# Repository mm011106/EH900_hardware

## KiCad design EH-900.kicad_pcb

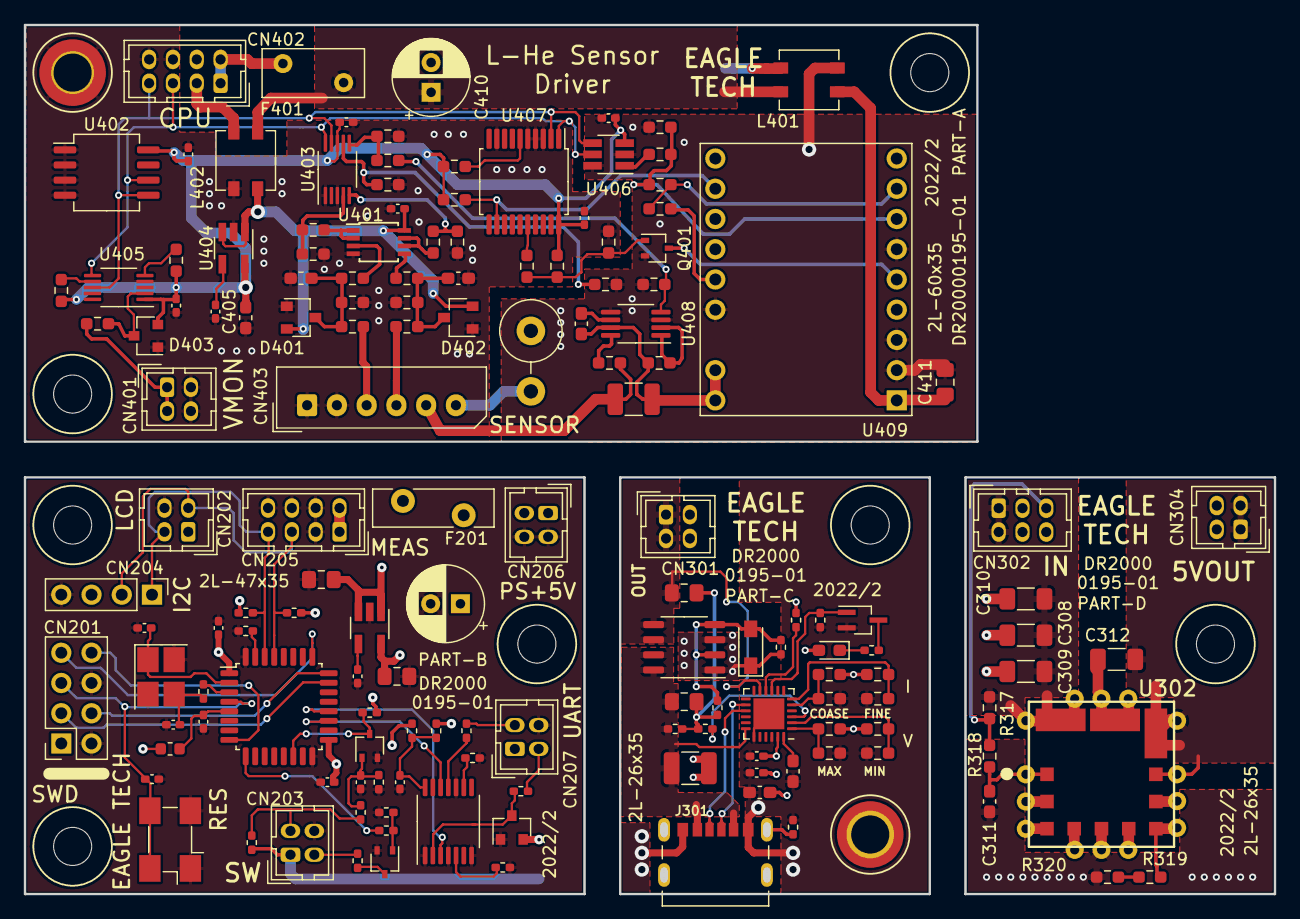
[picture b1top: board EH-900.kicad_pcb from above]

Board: 2 copper layers, 105.0 x 73.0 mm, 151 parts (0 on the bottom side), 101 nets.

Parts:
C201, C202: 6p; C_0402_1005Metric_Pad0.74x0.62mm_HandSolder
C203, C204, C205, C206, C208, C209, C303, C304, C402, C406, C407, C408, C409, C412: 0.1u/16V; C_0402_1005Metric_Pad0.74x0.62mm_HandSolder
C210, C410: 56u/10V/OS; CP_Radial_D6.3mm_P2.50mm
C211, C213: 4.7u/25V; C_0805_2012Metric_Pad1.18x1.45mm_HandSolder
C212, C405: 10n; C_0402_1005Metric_Pad0.74x0.62mm_HandSolder
C301, C306: 1u/50V; C_0603_1608Metric_Pad1.08x0.95mm_HandSolder
C302: 3.3u/50V; C_1210_3225Metric_Pad1.33x2.70mm_HandSolder
C305, C307: 1u/50V; C_0805_2012Metric_Pad1.18x1.45mm_HandSolder
C308, C309, C310, C312: 10u/25V; C_1206_3216Metric_Pad1.33x1.80mm_HandSolder
C311, C401, C413: 0.1u/50V; C_0603_1608Metric_Pad1.08x0.95mm_HandSolder
C403: 0.1u/50V; C_0603_1608Metric_Pad1.05x0.95mm_HandSolder
C404: 4.7u/25V; C_0603_1608Metric_Pad1.05x0.95mm_HandSolder
C411: 10u/25V; C_0805_2012Metric_Pad1.18x1.45mm_HandSolder
CN201: PH-2X4S; PinSocket_2x04_P2.54mm_Vertical
CN202, CN203, CN206, CN207, CN301, CN304, CN401: DF11-4DP-2DSA; Hirose_DF11-4DP-2DSA_2x02_P2.00mm_Vertical
CN204: 826646-4; PinHeader_1x04_P2.54mm_Vertical
CN205, CN402: DF11-8DP-2DSA; Hirose_DF11-8DP-2DSA_2x04_P2.00mm_Vertical
CN302: DF11-6DP-2DSA; Hirose_DF11-6DP-2DSA_2x03_P2.00mm_Vertical
CN403: 5267-06A; Molex_SPOX_5267-06A_1x06_P2.50mm_Vertical
D201, D403: 1SS226; SOT-23
D301: NZH10C-115; D_SOD-123F_HandSoldering
D302: KP-1608SYCK; D_0603_1608Metric_Pad1.05x0.95mm_HandSolder
D401, D402: 1SS379; D_SOT-236MOD_AKC
F201: RXEF075; Fuse_Bourns_MF-RHT400
F401: RXEF050; Fuse_Littelfuse_RXEF050_8.0x3.0x5.08LEAD
J301: UJC-HP-3-SMT-TR; CUI_UJC-HP-3-SMT-TR
L201: BLM18RK102SN1D; L_0603_1608Metric
L401, L402: ACM4520-142; L_CommonModeChoke_TDK_ACM4520
Q201, Q202, Q401: SSM3K15AFU; SOT-323_SC-70
Q301: IRF9362; SO-8_3.9x4.9mm_P1.27mm
Q302: Q_NMOS_DGS; SOT-323_SC-70_Handsoldering
R201, R203, R204: 10k; R_0402_1005Metric_Pad0.72x0.64mm_HandSolder
R202: 120; R_0402_1005Metric_Pad0.72x0.64mm_HandSolder
R205, R206, R208, R212, R213: 100k; R_0402_1005Metric_Pad0.72x0.64mm_HandSolder
R207: 1k; R_0402_1005Metric_Pad0.72x0.64mm_HandSolder
R209: 47k; R_0402_1005Metric_Pad0.72x0.64mm_HandSolder
R210: 330; R_0402_1005Metric_Pad0.72x0.64mm_HandSolder
R211: 4.7k; R_0402_1005Metric_Pad0.72x0.64mm_HandSolder
R214, R215: 100; R_0402_1005Metric_Pad0.72x0.64mm_HandSolder
R216, R314: 0; R_0402_1005Metric_Pad0.72x0.64mm_HandSolder
R217: ---; R_0402_1005Metric_Pad0.72x0.64mm_HandSolder
R301, R412, R414, R417: ---; R_0603_1608Metric_Pad0.98x0.95mm_HandSolder
R302, R304: 2.4k/THICK; R_0603_1608Metric_Pad0.98x0.95mm_HandSolder
R303: 3.6k/THICK; R_0603_1608Metric_Pad0.98x0.95mm_HandSolder
R305, R311: 10k/THICK; R_0402_1005Metric_Pad0.72x0.64mm_HandSolder
R306, R308: 5.1k/THICK; R_0603_1608Metric_Pad0.98x0.95mm_HandSolder
R307, R309, R319, R405, R406, R424: 1k/THICK; R_0603_1608Metric_Pad0.98x0.95mm_HandSolder
R310, R316: 1k/THICK; R_0402_1005Metric_Pad0.72x0.64mm_HandSolder
R312: 5.1k/THICK; R_0402_1005Metric_Pad0.72x0.64mm_HandSolder
R313: 51k/THICK; R_0402_1005Metric_Pad0.72x0.64mm_HandSolder
R315: 100k/THICK; R_0402_1005Metric_Pad0.72x0.64mm_HandSolder
R317, R318: 20k/THICK; R_0603_1608Metric_Pad0.98x0.95mm_HandSolder
R320: 330/THICK; R_0603_1608Metric_Pad0.98x0.95mm_HandSolder
R401, R403: 910k/THICK; R_0603_1608Metric_Pad0.98x0.95mm_HandSolder
R402, R404, R418, R423, R425, R430, R431: 100k/THICK; R_0603_1608Metric_Pad0.98x0.95mm_HandSolder
R407, R408: 6.2k; R_0603_1608Metric_Pad0.98x0.95mm_HandSolder
R409, R410: 4.3k; R_0603_1608Metric_Pad0.98x0.95mm_HandSolder
R411, R413, R422: 100/THICK; R_0603_1608Metric_Pad0.98x0.95mm_HandSolder
R415: 7.5k; R_0603_1608Metric_Pad0.98x0.95mm_HandSolder
R416: 2.2k; R_0603_1608Metric_Pad0.98x0.95mm_HandSolder
R419: 68/1W/LEAD; R_Axial_DIN0516_L15.5mm_D5.0mm_P5.08mm_Vertical
R420: 0; R_0603_1608Metric_Pad0.98x0.95mm_HandSolder
R421, R428: 49.9; R_0603_1608Metric_Pad0.98x0.95mm_HandSolder
R426: 100k; R_0603_1608Metric_Pad0.98x0.95mm_HandSolder
R427: 0.2/0.5W; R_1210_3225Metric_Pad1.30x2.65mm_HandSolder
R429: 4.99k; R_0603_1608Metric_Pad0.98x0.95mm_HandSolder
SW201: SKRPACE010; Oscillator_SMD_Fordahl_DFAS15-4Pin_5.0x3.2mm_HandSoldering
U201: STM32F303K8T6; LQFP-32_7x7mm_P0.8mm
U203: 74VHCT125AFT; TSSOP-14_4.4x5mm_P0.65mm
U204, U404: TPS79933DDC; SOT-23-5_HandSoldering
U301: CYPD3177-24LQXQ; QFN-24-1EP_4x4mm_P0.5mm_EP2.6x2.6mm
U302: OKL-T_3-W12N-C; OKLT3W12PC
U401: OPA2344EA; TSSOP-8_3x3mm_P0.65mm
U402: MB85RC256V; SO-8_5.3x6.2mm_P1.27mm
U403: ADS1115IDGS; VSSOP-10_3x3mm_P0.5mm
U405: DAC80501ZDGS; VSSOP-10_3x3mm_P0.5mm
U406: MCP4725A0T; SOT-23-6_Handsoldering
U407: MCP23008-xSS; SSOP-20_5.3x7.2mm_P0.65mm_microChip
U408: LTC6102CMS8; MSOP-8_3x3mm_P0.65mm
U409: LT3922; Converter_DCDC_StrawBerryLinux_LT3922
Y201: FA238-16MHz; Crystal_SMD_SeikoEpson_FA238-4Pin_3.2x2.5mm_HandSoldering

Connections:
+3V3A: C404.1, C406.1, C407.2, C408.1, C409.1, C412.2, D403.2, R418.1, R423.1, R425.1, R430.1, R431.1, U402.8, U403.8, U404.5, U405.1, U406.3, U407.20
+3V3D: C204.2, C205.1, C213.1, CN201.1, CN202.1, CN204.3, L201.2, R201.2, R203.2, R205.2, R217.2, U201.1, U201.17, U204.5
+5VA: C402.1, D401.2, D402.2, L402.2, U401.8, U404.1, U404.3
+5VD: C210.1, C211.1, CN203.1, CN205.1, CN205.2, CN207.1, D201.2, F201.1, R211.2, R216.2, U204.1, U204.3
/CPU/I2C1_SCL: CN202.2, CN204.2, CN205.5, R203.1, U201.29
/CPU/I2C1_SDA: CN202.3, CN204.1, CN205.7, R201.1, U201.30
/CPU/LED: R207.1, U201.9
/CPU/LED_DRIVE: CN203.2, R210.2
/CPU/NRST: C203.2, CN201.5, SW201.3, SW201.4, U201.4
/CPU/SWCLK: CN201.4, U201.24
/CPU/SWDIO: CN201.3, U201.23
/CPU/SWITCH: Q201.3, R205.1, U201.14
/CPU/SW_IN: CN203.3, R209.2, R211.1
/CPU/USART1_RX: U201.20, U203.3
/CPU/USART1_TX: U201.19, U203.12
/CPU/VCP_RX: CN201.7, U201.25
/CPU/VCP_TX: CN201.8, U201.8
/Measurement Unit/+VCC: C410.1, F401.2, L401.4, L402.3
/Measurement Unit/-VCC: C410.2, CN402.3, CN402.4, L401.3, L402.4
/Measurement Unit/DISABLE_IOUT: R424.2, U407.16
/Measurement Unit/EN: Q401.3, U409.5
/Measurement Unit/N_FAULT: R425.2, U407.12, U409.11
/Measurement Unit/SCL_MU: CN402.5, U402.6, U403.10, U405.6, U406.5, U407.1
/Measurement Unit/SDA_MU: CN402.7, U402.5, U403.9, U405.8, U406.4, U407.2
/Measurement Unit/Vrefout: R415.1, R420.2, U409.8
/Measurement Unit/Vset: R415.2, R416.1, R426.2, U409.7
/USB PD Power Supply/CC1: J301.A5, U301.15
/USB PD Power Supply/CC2: J301.B5, U301.14
/USB PD Power Supply/PD_3V3: C301.2, C303.2, C304.2, D302.2, R301.1, R303.1, R306.1, R308.1, R312.2, U301.23
GNDA: C401.2, C402.2, C403.2, C404.2, C405.2, C406.2, C407.1, C409.2, C412.1, CN401.3, CN401.4, CN402.6, CN402.8, CN403.1, CN403.2, D401.1, D402.1, D403.1, L402.1, R402.2, R404.1, R409.2, R410.2, R412.2, R414.2, R417.2, U401.4, U402.1, U402.2, U402.3, U402.4, U403.1, U403.3, U404.2, U405.4, U407.3, U407.4, U407.5, U407.9
GNDD: C201.1, C202.1, C203.1, C204.1, C205.2, C206.2, C208.2, C209.2, C210.2, C211.2, C212.2, C213.2, C301.1, C302.2, C303.1, C304.1, C306.1, C308.2, C309.2, C310.2, C311.1, C312.2, CN201.2, CN201.6, CN202.4, CN203.4, CN204.4, CN205.3, CN205.4, CN205.6, CN205.8, CN206.3, CN206.4, CN207.4, CN301.3, CN301.4, CN302.3, CN302.4, CN302.6, CN304.3, CN304.4, D201.1, J301.A12, J301.B12, Q201.2, Q202.2, Q302.2, R204.1, R206.1, R208.1, R212.1, R213.1, R302.2, R304.2, R305.2, R307.2, R309.2, R315.2, R320.2, SW201.1, SW201.2, U201.16, U201.32, U203.1, U203.4, U203.7, U203.10, U203.13, U204.2, U301.19, U301.22, U301.25, U302.3, U302.7, Y201.2, Y201.4
GNDHV: C408.2, C411.2, L401.2, Q401.2, R413.1, R416.2, R419.1, R429.1, U406.2, U406.6, U408.3, U408.5, U409.2, U409.3, U409.6, U409.15
unnamed: C201.2, U201.2, Y201.1
unnamed: C202.2, R202.2, Y201.3
unnamed: C206.1, L201.1, U201.5
unnamed: C208.1, Q201.1, R206.2, R209.1
unnamed: C209.1, R216.1, R217.1, U203.14
unnamed: C212.1, U204.4
unnamed: C302.1, C305.1, J301.A9, J301.B9, Q301.7, Q301.8, R311.1, U301.18
unnamed: C305.2, C307.2, R310.1, R311.2, R314.2
unnamed: C306.2, U301.24
unnamed: C307.1, CN301.1, CN301.2, Q301.5, Q301.6, U301.11
unnamed: C308.1, C309.1, C310.1, CN302.1, CN302.2, R317.2, U302.2
unnamed: C311.2, R318.1, U302.1
unnamed: C312.1, CN304.1, CN304.2, U302.4, U302.5
unnamed: C401.1, D402.3, R401.2, R402.1, R406.2
unnamed: C403.1, D401.3, R403.2, R404.2, R405.2
unnamed: C405.1, U404.4
unnamed: C411.1, L401.1, U409.1
unnamed: C413.1, R427.2, R428.1, U408.7, U409.17, U409.18
unnamed: C413.2, U408.6
unnamed: CN206.1, CN206.2, F201.2
unnamed: CN207.2, R215.2
unnamed: CN207.3, R214.2
unnamed: CN302.5, R317.1, R318.2
unnamed: CN401.1, CN401.2, R422.1
unnamed: CN402.1, CN402.2, F401.1
unnamed: CN403.3, R403.1
unnamed: CN403.4, R401.1
unnamed: CN403.5, R421.1, R427.1
unnamed: CN403.6, R419.2
unnamed: D201.3, R215.1, U203.2
unnamed: D301.1, Q301.1, Q301.3, R313.1
unnamed: D301.2, Q301.2, Q301.4, R313.2, R314.1
unnamed: D302.1, R316.1
unnamed: D403.3, R422.2, U405.2
unnamed: J301.S1, J301.S2, J301.S3, J301.S4, R305.1
unnamed: Q202.1, R207.2, R208.2
unnamed: Q202.3, R210.1
unnamed: Q302.1, R315.1, U301.9
unnamed: Q302.3, R316.2
unnamed: Q401.1, R417.1, R418.2, R424.1
unnamed: R202.1, U201.3
unnamed: R204.2, U201.31
unnamed: R212.2, U203.5
unnamed: R213.2, U203.9
unnamed: R214.1, U203.11
unnamed: R301.2, R302.1, U301.6
unnamed: R303.2, R304.1, U301.5
unnamed: R306.2, R307.1, U301.2
unnamed: R308.2, R309.1, U301.1
unnamed: R310.2, U301.3
unnamed: R312.1, U301.10
unnamed: R319.1, U302.6
unnamed: R319.2, R320.1
unnamed: R405.1, U401.3
unnamed: R406.1, U401.5
unnamed: R407.1, R410.1, U403.4
unnamed: R407.2, U401.1, U401.2
unnamed: R408.1, R409.1, U403.5
unnamed: R408.2, U401.6, U401.7
unnamed: R411.1, R429.2, U408.4
unnamed: R411.2, R412.1, U403.6
unnamed: R413.2, R414.1, U403.7
unnamed: R420.1, U409.14
unnamed: R421.2, U408.8
unnamed: R423.2, U407.6
unnamed: R426.1, U406.1
unnamed: R428.2, U408.1, U408.2
unnamed: R430.2, U405.5
unnamed: R431.2, U405.7

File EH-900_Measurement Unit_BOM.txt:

"Source:"	"/Users/masakazumiyamoto/Box/KiCAD/project/EH-900/EH-900.sch"
"Date:"	"Friday, 29 October 2021 at 11:36:21"
"Tool:"	"Eeschema (5.1.10-1-10_14)"
"Component Count in total:"	"140"
"Ref"	"Value"	"Part"	"Package"	"Size"
"C401"	"0.1u/50V"	"50V"	"SMD"	"1608"
"C402"	"0.1u/16V"	""	""	"1005"
"C403"	"0.1u/50V"	"50V"	"SMD"	"1608"
"C404"	"4.7u/25V"	"25V"	"SMD"	"1608"
"C405"	"10n"	"50V"	"SMD"	"1608"
"C406"	"0.1u/16V"	""	""	"1005"
"C407"	"0.1u/16V"	""	""	"1005"
"C408"	"0.1u/16V"	""	""	"1005"
"C409"	"0.1u/16V"	""	""	"1005"
"C410"	"56u/10V/OS"	""	""	""
"C411"	"10u/25V"	"25V"	"SMD"	"3216"
"C412"	"0.1u/16V"	"16V"	"SMD"	"1005"
"C413"	"0.1u/50V"	"50V"	"SMD"	"1608"
"CN401"	"DF11-4DP-2DSA"	""	""	""
"CN402"	"DF11-8DP-2DSA"	""	""	""
"CN403"	"5267-06A"	""	""	""
"D401"	"1SS379"	""	""	""
"D402"	"1SS379"	""	""	""
"D403"	"1SS226"	""	""	""
"F401"	"RXEF050"	""	""	""
"L401"	"ACM4520-142"	""	""	""
"L402"	"ACM4520-142"	""	""	""
"Q401"	"SSM3K15AFU"	""	""	""
"R401"	"910k/THICK"	""	"SMD"	"1608"
"R402"	"10k"	""	"SMD"	"1608"
"R403"	"910k/THICK"	""	"SMD"	"1608"
"R404"	"10k"	""	"SMD"	"1608"
"R405"	"1k/THICK"	""	"SMD"	"1608"
"R406"	"1k/THICK"	""	"SMD"	"1608"
"R407"	"6.2k"	""	"SMD"	"1608"
"R408"	"6.2k"	""	"SMD"	"1608"
"R409"	"4.3k"	""	"SMD"	"1608"
"R410"	"4.3k"	""	"SMD"	"1608"
"R411"	"100/THICK"	""	"SMD"	"1608"
"R412"	"---"	""	"SMD"	"1608"
"R413"	"100/THICK"	""	"SMD"	"1608"
"R414"	"---"	""	"SMD"	"1608"
"R415"	"7.5k"	""	"SMD"	"1608"
"R416"	"2.2k"	""	"SMD"	"1608"
"R417"	"---"	""	"SMD"	"1608"
"R418"	"100k/THICK"	""	"SMD"	"1608"
"R419"	"68/1W/LEAD"	""	"DIP"	""
"R420"	"0"	""	"SMD"	"1608"
"R421"	"49.9"	""	"SMD"	"1608"
"R422"	"100/THICK"	""	"SMD"	"1608"
"R423"	"100k/THICK"	""	"SMD"	"1608"
"R424"	"1k/THICK"	""	"SMD"	"1608"
"R425"	"100k/THICK"	""	"SMD"	"1608"
"R426"	"100k"	""	"SMD"	"1608"
"R427"	"0.2/0.5W"	""	"SMD"	"3225"
"R428"	"49.9"	""	"SMD"	"1608"
"R429"	"4.99k"	""	"SMD"	"1608"
"R430"	"100k/THICK"	""	"SMD"	"1608"
"R431"	"100k/THICK"	""	"SMD"	"1608"
"U401"	"OPA2344EA"	""	""	""
"U402"	"MB85RC256V"	""	""	""
"U403"	"ADS1115IDGS"	""	""	""
"U404"	"TPS79933DDC"	""	""	""
"U405"	"DAC80501ZDGS"	""	""	""
"U406"	"MCP4725A0T"	""	""	""
"U407"	"MCP23008-xSS"	""	""	""
"U408"	"LTC6102CMS8"	""	""	""
"U409"	"LT3922"	""	""	""

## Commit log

2022-04-15 Create LICENSE
2022-04-19 Change license to CC BY 4.0
2022-04-19 upload local files
2022-04-19 revise location of files
2022-04-20 artwork was completed
2022-04-20 organaize symbol libs
2023-06-14 Rev.01-Add USB-PD CKT
2023-06-14 Update LICENSE
